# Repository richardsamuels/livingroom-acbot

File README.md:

# AC Bot
An ESPHome-based robot to integrate my GE AEL08LQQ2 window AC into Home Assistant.

## Custom PCB

A custom PCB can be found in ./PCB. The expected servo pinout is (Control, 5V, GND),
where Control is indicated on the silkscreen with a solid colored pin.

## BOM

Note: This BOM does not include parts on custom PCB. See the JLCPCB-compatible
[PCB BOM](PCB/jlcpcb/production_files/BOM-esp.csv) for those items, which can
be used to purchase a fully assembled PCB from JLCPCB.

| Part                                                             | Quantity |
| ---------------------------------------------------------------- | -------- |
| SG90 Servo                                                       | 2        |
| M2.5x6 SHCS                                                      | 4        |
| M2x10 self-tapping screws                                        | 5        |
| [~Photoresistor~*](https://www.amazon.com/gp/product/B01N7V536K) | 1        |
| STL/panel.stl, any stiff filament (ABS, PLA, or PETG)            | 1        |
| STL/power-pusher.stl, any stiff filament (ABS, PLA, or PETG)     | 2        |

* The original version of this PCB used a photoresistor to detect the on/off
state of the AC, see below for the flaws of this approach

## 3D Printed Parts

1. Connect all servos to the flashed PCB and apply power via USB-C to zero the
servo positions.
2. To each servo, attach power-pusher.stl to the servo horn with a single arm
using M2x10 self-tappers. Use the hole farthest from the center, and third from
the end.
3. Attach servos with M2.5x6 SHCS bolts to panel.stl. Screw directly into the
plastic.
4. Using VHB, or similarly strong double-sided sticky tape, attach directly to
AC's front panel, ensuring alignment with the power, temperature read out, and
temperature control buttons.
5. Press the panel down with even more force to ensure the servos will not push
the printed parts off the front panel.

## Failed Approaches
1. This project originally used a photoresistor to detect when the temperature
readout was lit to infer the on/off state of the air conditioner. This approach
proved unreliable because the outer plastic shell of the airconditioner is
translucent to sunlight, and would provide false indications when the sun
shined directly on the air conditioner's shell.

This was remediated with an [Aqara Smart Plug](https://www.amazon.com/gp/product/B07CJ2MM6Z)
which reports the power consumption in watts.. If the AC is consuming more than
50 watts, it is considered to be on; otherwise, it is considered to be off.

2 . The original version of this project offered the ability to change the
temperature instead of the AC mode (Cool/Energy Save/Fan). After putting v1
into action, I did not use the remote temperature change functionality, but
wanted to change the mode. This functionality was dropped, and the servo was
repurposed to allow changing the mode instead.

## Future Work
1. Change the AC Mode instead of turning off the entire unit when Home
Assistant's thermostat is used.
2. Design a proper mounting mechanism for the PCB, and a cover for the whole
unit

# Setup & Flashing
## Setup
1. `python -m venv venv`
2. `./venv/bin/activate`
3. `python -m pip install esphome`
## Flashing
`esphome run livingroom-acbot.yaml`

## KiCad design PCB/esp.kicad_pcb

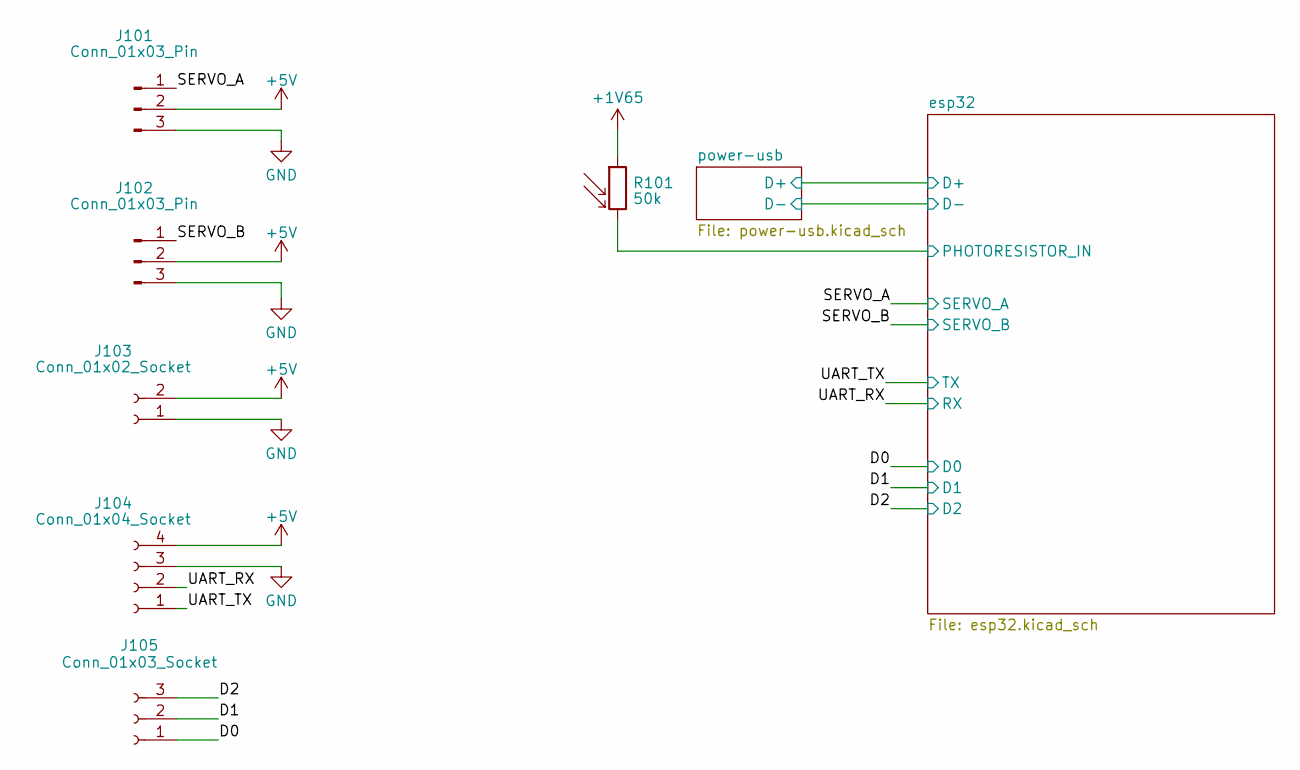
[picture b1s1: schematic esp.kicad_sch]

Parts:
J101, J102: Conn_01x03_Pin; PinHeader_1x03_P2.54mm_Horizontal
J103: Conn_01x02_Socket; PinHeader_1x02_P2.54mm_Vertical
J104: Conn_01x04_Socket; PinSocket_1x04_P2.00mm_Vertical
J105: Conn_01x03_Socket; PinHeader_1x03_P2.54mm_Vertical
R101: 50k; PinHeader_1x02_P2.54mm_Vertical

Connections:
+1V65: R101.1; also elsewhere on the board
+5V: J101.2, J102.2, J103.2, J104.4; also elsewhere on the board
/D0: J105.1; also elsewhere on the board
/D1: J105.2; also elsewhere on the board
/D2: J105.3; also elsewhere on the board
/SERVO_A: J101.1; also elsewhere on the board
/SERVO_B: J102.1; also elsewhere on the board
/UART_RX: J104.2; also elsewhere on the board
/UART_TX: J104.1; also elsewhere on the board
/esp32/PHOTORESISTOR_IN: R101.2; also elsewhere on the board
GND: J101.3, J102.3, J103.1, J104.3; also elsewhere on the board

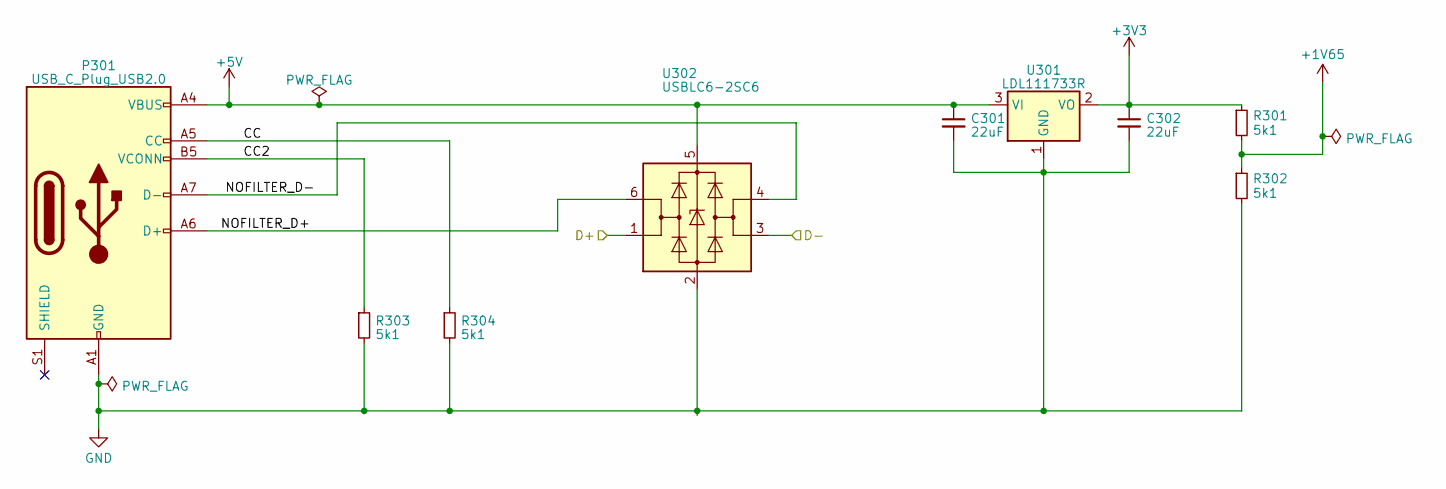
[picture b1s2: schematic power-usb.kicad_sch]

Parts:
C301, C302: 22uF; C_1206_3216Metric
P301: USB_C_Plug_USB2.0; USB_C_Receptacle_HRO_TYPE-C-31-M-12
R301, R302, R303, R304: 5k1; R_0402_1005Metric
U301: LDL111733R; SOT-223-3_TabPin2
U302: USBLC6-2SC6; SOT-23-6

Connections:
+1V65: R301.2, R302.1; also elsewhere on the board
+3V3: C302.1, R301.1, U301.2 (VO); also elsewhere on the board
+5V: C301.1, P301.A4 (VBUS), P301.A9 (VBUS), P301.B4 (VBUS), P301.B9 (VBUS), U301.3 (VI), U302.5 (VBUS); also elsewhere on the board
/esp32/D+: U302.1 (I/O1); also elsewhere on the board
/esp32/D-: U302.3 (I/O2); also elsewhere on the board
/power-usb/CC: P301.A5 (CC), R304.1
/power-usb/CC2: P301.B5 (VCONN), R303.1
/power-usb/NOFILTER_D+: P301.A6 (D+), P301.B6 (D+), U302.6 (I/O1)
/power-usb/NOFILTER_D-: P301.A7 (D-), P301.B7 (D-), U302.4 (I/O2)
GND: C301.2, C302.2, P301.A1 (GND), P301.A12 (GND), P301.B1 (GND), P301.B12 (GND), R302.2, R303.2, R304.2, U301.1 (GND), U302.2 (GND); also elsewhere on the board

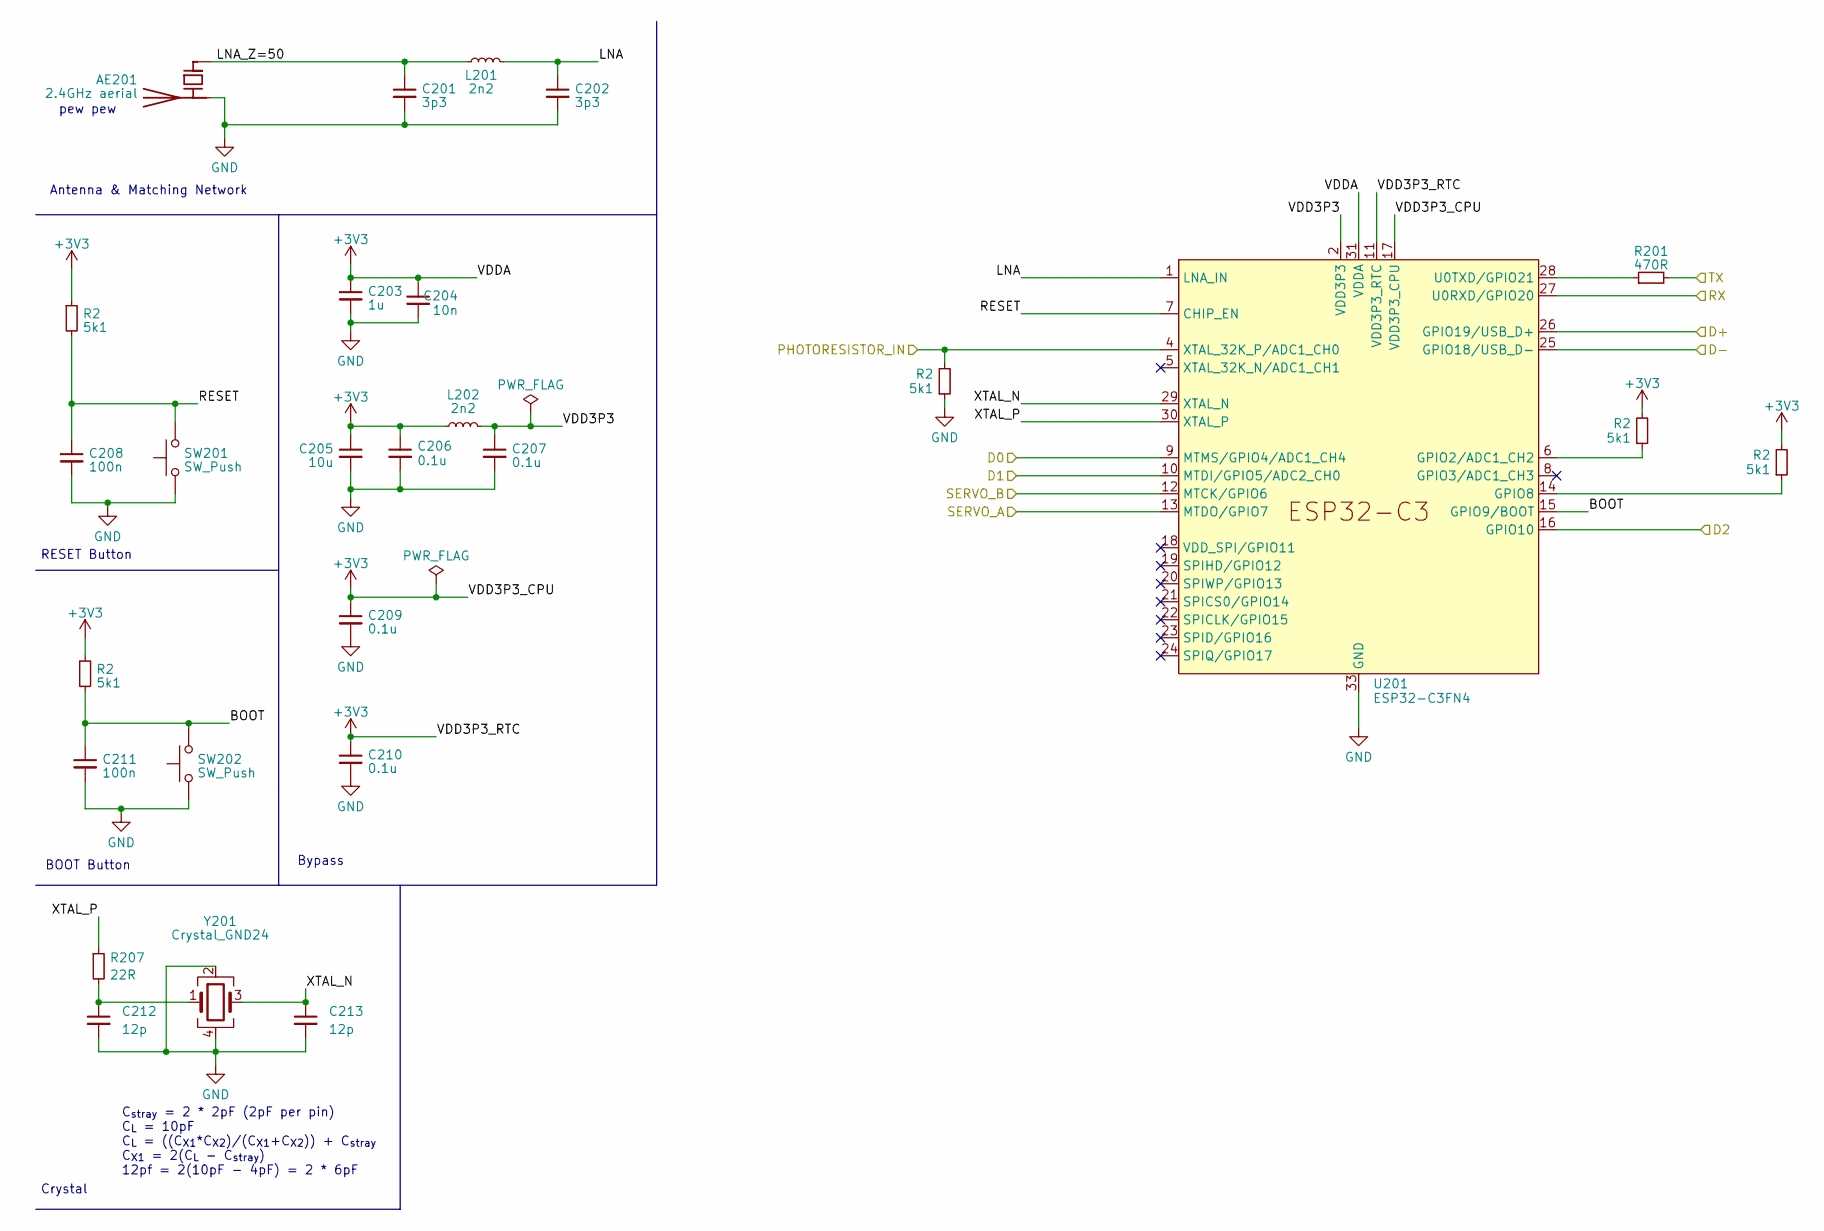
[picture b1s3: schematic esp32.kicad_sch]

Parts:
AE201: 2.4GHz aerial; Texas_SWRU120D_InvF_2.4GHz_Right
C201, C202: 3p3; C_0402_1005Metric
C203: 1u; C_0402_1005Metric
C204: 10n; C_0402_1005Metric
C205: 10u; C_0402_1005Metric
C206, C207, C209, C210: 0.1u; C_0402_1005Metric
C208, C211: 100n; C_0402_1005Metric
C212, C213: 12p; C_0402_1005Metric
L201, L202: 2n2; L_0603_1608Metric
R2: 5k1; R_0402_1005Metric
R201: 470R; R_0402_1005Metric
R207: 22R; R_0402_1005Metric
SW201, SW202: SW_Push; SW_SPST_PTS810
U201: ESP32-C3FN4; QFN-32-1EP_5x5mm_P0.5mm_EP3.45x3.45mm
Y201: Crystal_GND24; Crystal_SMD_2016-4Pin_2.0x1.6mm

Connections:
+3V3: C203.1, C204.1, C205.1, C206.1, C209.1, C210.1, L202.1, U201.11 (VDD3P3_RTC), U201.17 (VDD3P3_CPU), U201.31 (VDDA), U201.32 (VDDA); also elsewhere on the board
/D0: U201.9 (MTMS/GPIO4/ADC1_CH4); also elsewhere on the board
/D1: U201.10 (MTDI/GPIO5/ADC2_CH0); also elsewhere on the board
/D2: U201.16 (GPIO10); also elsewhere on the board
/SERVO_A: U201.13 (MTDO/GPIO7); also elsewhere on the board
/SERVO_B: U201.12 (MTCK/GPIO6); also elsewhere on the board
/UART_RX: U201.27 (U0RXD/GPIO20); also elsewhere on the board
/UART_TX: R201.2; also elsewhere on the board
/esp32/BOOT: C211.1, SW202.2, U201.15 (GPIO9/BOOT); also elsewhere on the board
/esp32/D+: U201.26 (GPIO19/USB_D+); also elsewhere on the board
/esp32/D-: U201.25 (GPIO18/USB_D-); also elsewhere on the board
/esp32/LNA: C202.1, L201.2, U201.1 (LNA_IN)
/esp32/LNA_Z=50: AE201.1 (FEED), C201.1, L201.1
/esp32/PHOTORESISTOR_IN: U201.4 (XTAL_32K_P/ADC1_CH0); also elsewhere on the board
/esp32/RESET: C208.1, SW201.2, U201.7 (CHIP_EN); also elsewhere on the board
/esp32/VDD3P3: C207.1, L202.2, U201.2 (VDD3P3), U201.3 (VDD3P3)
/esp32/XTAL_N: C213.1, U201.29 (XTAL_N), Y201.3
/esp32/XTAL_P: R207.1, U201.30 (XTAL_P)
GND: AE201.2 (PCB_Trace), C201.2, C202.2, C203.2, C204.2, C205.2, C206.2, C207.2, C208.2, C209.2, C210.2, C211.2, C212.2, C213.2, SW201.1, SW202.1, U201.33 (GND), Y201.2, Y201.4; also elsewhere on the board
unnamed: C212.1, R207.2, Y201.1
unnamed 26: U201.6 (GPIO2/ADC1_CH2); also elsewhere on the board
unnamed 27: U201.14 (GPIO8); also elsewhere on the board
unnamed: R201.1, U201.28 (U0TXD/GPIO21)

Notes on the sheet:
Antenna & Matching Network
C_{stray} = 2 * 2pF (2pF per pin) C_{L} = 10pF C_{L} = ((C_{X1}*C_{X2})/(C_{X1}+C_{X2})) + C_{stray} C_{X1} = 2(C_{L} - C_{stray}) 12pf = 2(10pF - 4pF) = 2 * 6pF
Crystal
RESET Button
Bypass
BOOT Button
pew pew

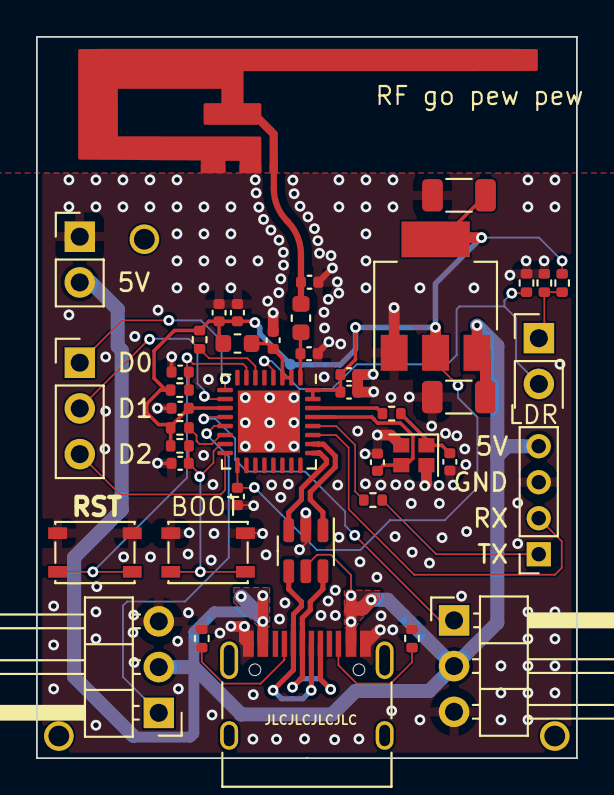
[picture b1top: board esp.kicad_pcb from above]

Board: 4 copper layers, 30.0 x 40.1 mm, 42 parts (0 on the bottom side), 29 nets.

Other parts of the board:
R202, R203, R204, R205, R206: 5k1; R_0402_1005Metric

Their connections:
+3V3: R202.1, R204.2, R205.2, R206.1; also elsewhere on the board
/esp32/BOOT: R206.2; also elsewhere on the board
/esp32/PHOTORESISTOR_IN: R203.2; also elsewhere on the board
/esp32/RESET: R202.2; also elsewhere on the board
GND: R203.1; also elsewhere on the board
unnamed 26: R204.1; also elsewhere on the board
unnamed 27: R205.1; also elsewhere on the board

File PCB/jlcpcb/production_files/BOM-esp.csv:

Comment,Designator,Footprint,LCSC
22uF,"C301,C302",C_1206_3216Metric,C12891
10n,C204,C_0402_1005Metric,C15195
0.1u,"C206,C207,C208,C209,C210,C211",C_0402_1005Metric,C1525
12p,"C212,C213",C_0402_1005Metric,C1547
10u,C205,C_0402_1005Metric,C15525
3p3,"C201,C202",C_0402_1005Metric,C1565
USB_C_Plug_USB2.0,P301,USB_C_Receptacle_HRO_TYPE-C-31-M-12,C165948
22R,R207,R_0402_1005Metric,C25092
470R,R201,R_0402_1005Metric,C25117
Crystal_GND24,Y201,Crystal_SMD_2016-4Pin_2.0x1.6mm,C255898
5k1,"R202,R203,R204,R205,R206,R301,R302,R303,R304",R_0402_1005Metric,C25905
2n2,"L201,L202",L_0603_1608Metric,C29682
LDL111733R,U301,SOT-223-3_TabPin2,C435835
SW_Push,"SW201,SW202",SW_SPST_PTS810,C470426
ESP32-C3FN4,U201,QFN-32-1EP_5x5mm_P0.5mm_EP3.45x3.45mm,C5143572
1u,C203,C_0402_1005Metric,C52923
USBLC6-2SC6,U302,SOT-23-6,C7519
Conn_01x03_Pin,"J101,J102",PinHeader_1x03_P2.54mm_Horizontal,C92159
50k,R101,PinHeader_1x02_P2.54mm_Vertical,
2.4GHz aerial,AE201,Texas_SWRU120D_InvF_2.4GHz_Right,
Conn_01x04_Socket,J104,PinSocket_1x04_P2.00mm_Vertical,
Conn_01x03_Socket,J105,PinHeader_1x03_P2.54mm_Vertical,
Conn_01x02_Socket,J103,PinHeader_1x02_P2.54mm_Vertical,

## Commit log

2023-05-29 Prototype w/ FREENOVE ESP32-WROVER cam board
2023-05-29 ignore secrets
2023-05-29 Add workflow
2023-05-29 Add secrets.yaml
2023-05-29 remove duplicate
2023-05-29 make key base64
2023-05-29 fix again
2023-05-29 Add CI workflow (#1)
2023-06-07 use a pull down for the adc
2023-06-08 Add custom PCB config
2023-06-29 c3 board
2023-07-10 almost working; hangs on boot
2023-07-25 add PCB
2023-07-25 Add Images, STL and README
2023-07-25 fix table
2023-07-25 add fusion 360 image
2023-07-25 license
2023-07-25 exif purge
2023-07-25 Fix CI
2023-07-25 Bump esphome/build-action
2023-07-25 Add Custom PCB (#2)
2024-01-24 v2, with mode basic mode control
2024-01-24 add setup instructions
2024-01-24 cleanup unused platforms
2024-01-24 cleanup secrets.yaml generation during CI
2024-01-24 minor corrections in README
2024-01-25 V2, with support for mode changing (#3)
